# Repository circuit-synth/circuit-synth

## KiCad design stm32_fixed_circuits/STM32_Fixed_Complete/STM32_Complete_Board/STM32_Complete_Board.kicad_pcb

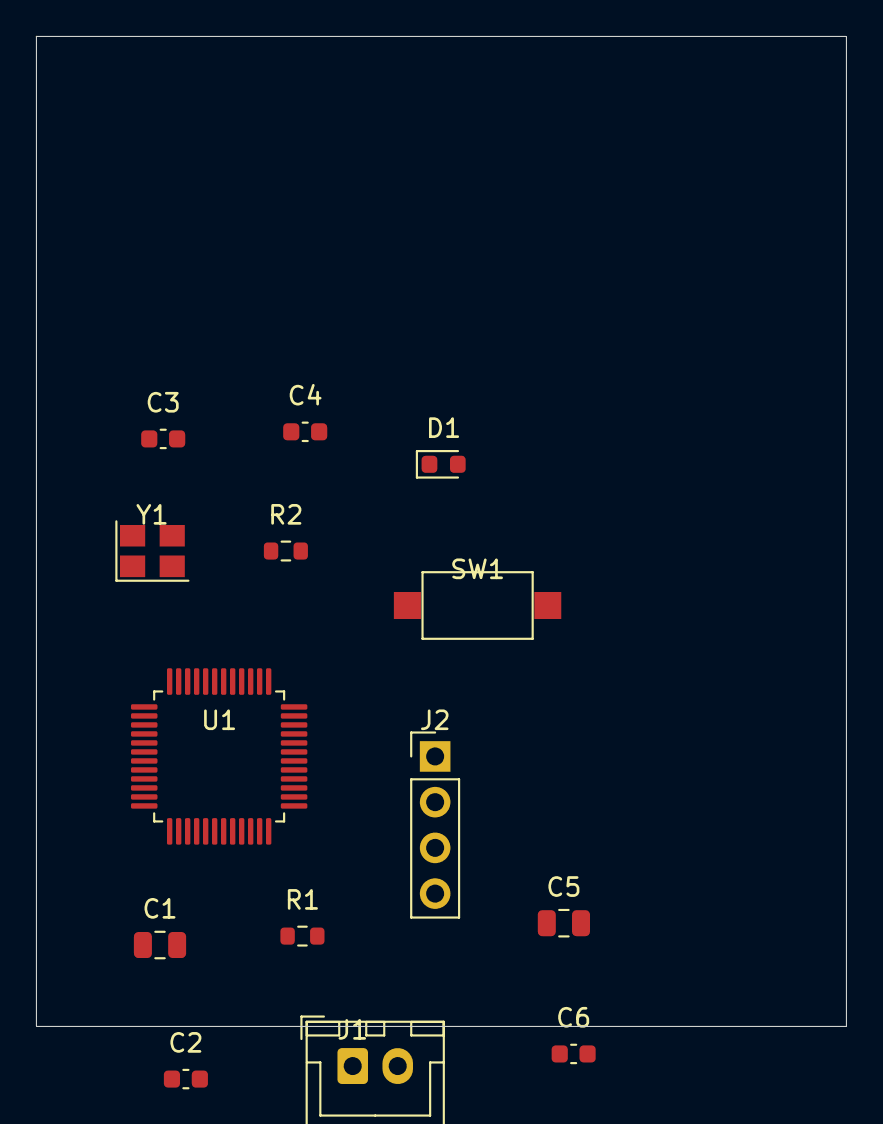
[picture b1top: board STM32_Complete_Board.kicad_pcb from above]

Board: 2 copper layers, 45.0 x 55.0 mm, 14 parts (0 on the bottom side), 9 nets, no tracks yet.

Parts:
C1, C5: 10uF; C_0805_2012Metric
C2, C6: 100nF; C_0603_1608Metric
C3, C4: 18pF; C_0603_1608Metric
D1: LED_0603_1608Metric
J1: JST_XH_B2B-XH-A_1x02_P2.50mm_Vertical
J2: PinHeader_1x04_P2.54mm_Vertical
R1: 10k; R_0603_1608Metric
R2: 220; R_0603_1608Metric
SW1: SW_SPST_CK_RS282G05A3
U1: LQFP-48_7x7mm_P0.5mm
Y1: 8MHz; Crystal_SMD_3225-4Pin_3.2x2.5mm

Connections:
GND: C1.2, C2.2, C3.2, C4.2, C5.2, C6.2, D1.1, J1.2, J2.2, SW1.2, U1.8, U1.23, U1.35, U1.47
LED_CONTROL: R2.1, U1.15
unnamed: C3.1, U1.5, Y1.1
unnamed: C4.1, U1.6, Y1.2
unnamed: D1.2, R2.2
SWCLK: J2.4, U1.37
SWDIO: J2.3, U1.34
VCC_3V3: C1.1, C2.1, C5.1, C6.1, J1.1, J2.1, R1.1, U1.9, U1.24, U1.36, U1.48
nRESET: R1.2, SW1.1, U1.7
